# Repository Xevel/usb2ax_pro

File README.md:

# usb2ax_pro
Fast USB interface for robotics servos (Dynamixel)

## License
Code is under MIT License.

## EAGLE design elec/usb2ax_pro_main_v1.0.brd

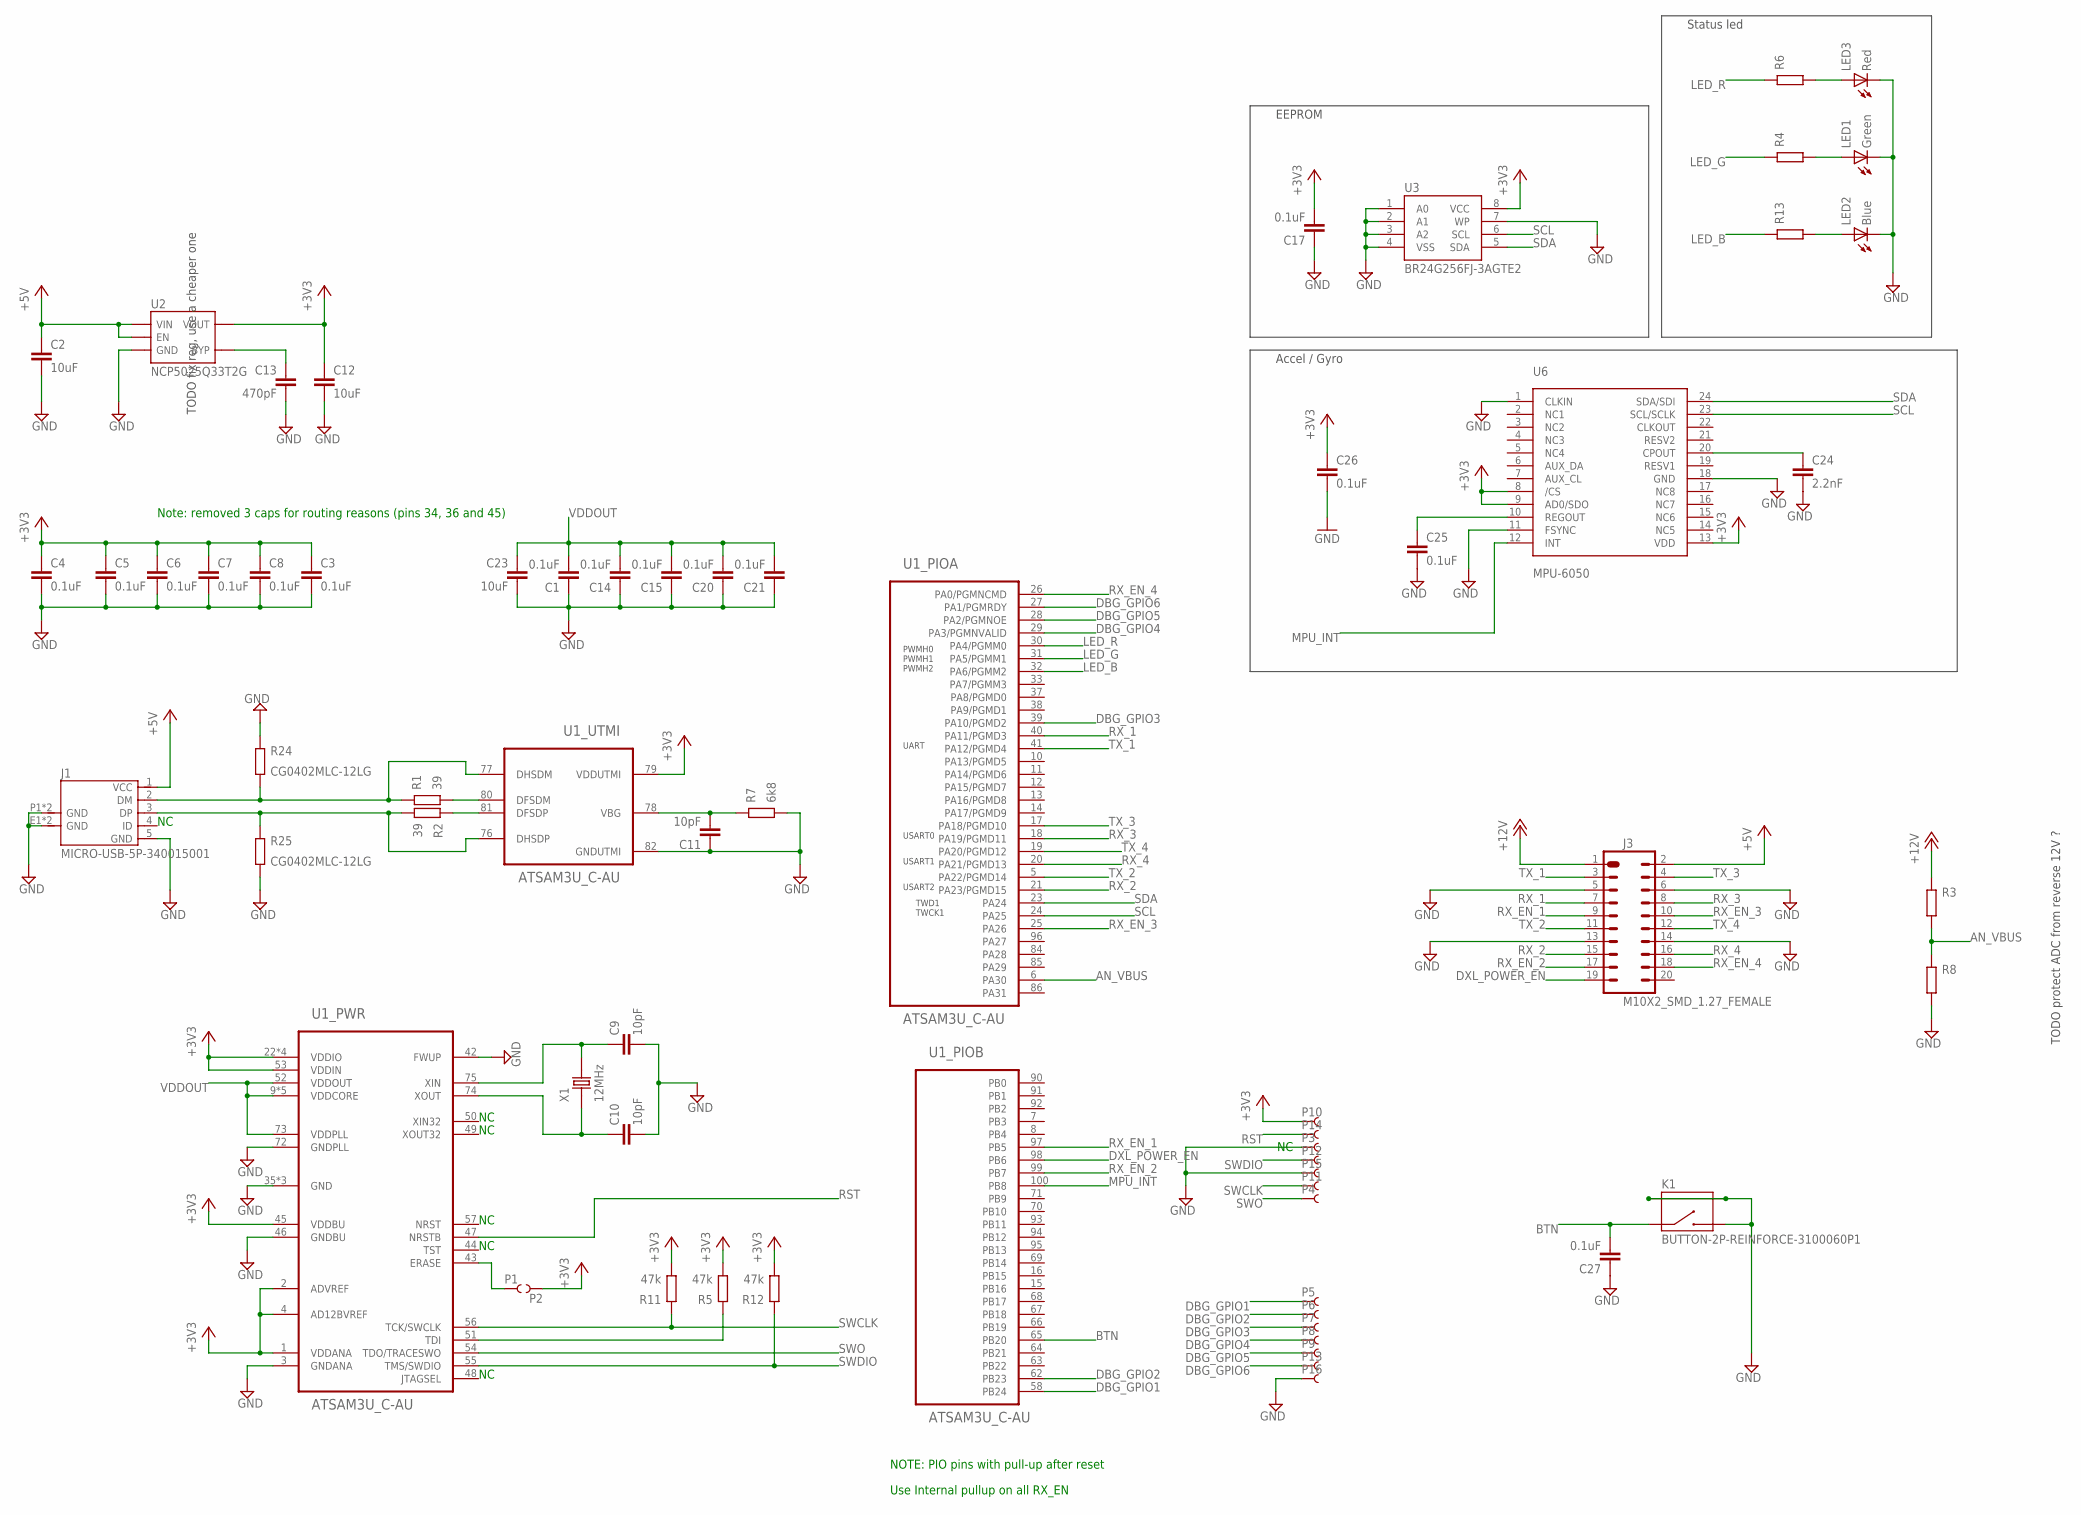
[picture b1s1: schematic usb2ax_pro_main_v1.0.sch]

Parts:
C1, C3, C4, C5, C6, C7, C8, C14, C15, C17, C20, C21, C25, C26, C27: 0.1uF; 0201_N
C2, C12, C23: 10uF; 0805_N
C9, C10, C11: 10pF; 0201_N
C13: 470pF; 0201_N
C24: 2.2nF; 0201_N
J1: MICRO-USB-5P-340015001; B-SMD-5P
J3: M10X2_SMD_1.27_FEMALE; 2X10_SMD_1.27_FEMALE
K1: BUTTON-2P-REINFORCE-3100060P1; 4P-SMD-7.0X3.5X3.5H-90D
LED1: Green; D_0603_N
LED2: Blue; D_0603_N
LED3: Red; D_0603_N
P1, P2: PIN_SMD_2X2.5
P3, P4, P10, P11, P12, P14, P15: PIN_SMD_0.8X1.6
P5, P6, P7, P8, P9, P13, P16: PIN_SMD_1X2
R1, R2: 39; 0201_N
R3, R4, R6, R8, R13: R0201; 0201_N
R5, R11, R12: 47k; 0201_N
R7: 6k8; 0201_N
R24, R25: CG0402MLC-12LG; 0402_N
U1: ATSAM3U_C-AU; QFP50P1600X1600-100N
U2: NCP5025Q33T2G; SC70-5
U3: BR24G256FJ-3AGTE2; SO08
U6: MPU-6050; QFN-24
X1: 12MHz; 2P-SMD-5.0X3.2

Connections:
+3V3: C3.1, C4.1, C5.1, C6.1, C7.1, C8.1, C12.1, C17.2, C26.1, P2.PIN, P10.PIN, R5.1, R11.1, R12.1, U1.1 (VDDANA), U1.2 (ADVREF), U1.4 (AD12BVREF), U1.22 (VDDIO), U1.36 (VDDIO), U1.45 (VDDBU), U1.53 (VDDIN), U1.60 (VDDIO), U1.79 (VDDUTMI), U1.88 (VDDIO), U2.5 (VOUT), U3.8 (VCC), U6.8 (/CS), U6.9 (AD0/SDO), U6.13 (VDD)
+5V: C2.1, J1.1 (VCC), J3.2, U2.1 (VIN), U2.3 (EN)
+12V: J3.1, R3.2
AN_VBUS: R3.1, R8.2, U1.6 (PA30)
BTN: C27.2, K1.1, U1.65 (PB20)
DBG_GPIO1: P5.P$1, U1.58 (PB24)
DBG_GPIO2: P6.P$1, U1.62 (PB23)
DBG_GPIO3: P7.P$1, U1.39 (PA10/PGMD2)
DBG_GPIO4: P8.P$1, U1.29 (PA3/PGMNVALID)
DBG_GPIO5: P9.P$1, U1.28 (PA2/PGMNOE)
DBG_GPIO6: P13.P$1, U1.27 (PA1/PGMRDY)
DXL_POWER_EN: J3.19, U1.98 (PB6)
GND: C1.1, C2.2, C3.2, C4.2, C5.2, C6.2, C7.2, C8.2, C9.2, C10.2, C11.1, C12.2, C13.2, C14.1, C15.1, C17.1, C20.1, C21.1, C23.2, C24.2, C25.2, C26.2, C27.1, J1.5 (GND), J1.E1 (GND), J1.E2 (GND), J1.P1 (GND), J1.P2 (GND), J3.5, J3.6, J3.13, J3.14, K1.2, K1.S1, K1.S2, LED1.C, LED2.C, LED3.C, P3.PIN, P15.PIN, P16.P$1, R7.1, R8.1, R24.2, R25.1, U1.3 (GNDANA), U1.35 (GND), U1.42 (FWUP), U1.46 (GNDBU), U1.61 (GND), U1.72 (GNDPLL), U1.82 (GNDUTMI), U1.89 (GND), U2.2 (GND), U3.1 (A0), U3.2 (A1), U3.3 (A2), U3.4 (VSS), U3.7 (WP), U6.1 (CLKIN), U6.11 (FSYNC), U6.18 (GND)
LED_B: R13.2, U1.32 (PA6/PGMM2)
LED_G: R4.2, U1.31 (PA5/PGMM1)
LED_R: R6.2, U1.30 (PA4/PGMM0)
MPU_INT: U1.100 (PB8), U6.12 (INT)
unnamed: J1.2 (DM), R1.2, R24.1, U1.77 (DHSDM)
unnamed: J1.3 (DP), R2.1, R25.2, U1.76 (DHSDP)
unnamed: R2.2, U1.81 (DFSDP)
unnamed: R1.1, U1.80 (DFSDM)
unnamed: LED3.A, R6.1
unnamed: LED2.A, R13.1
unnamed: LED1.A, R4.1
unnamed: C9.1, U1.75 (XIN), X1.2
unnamed: C10.1, U1.74 (XOUT), X1.1
unnamed: P1.PIN, U1.43 (ERASE)
unnamed: C13.1, U2.4 (BYP)
unnamed: C11.2, R7.2, U1.78 (VBG)
unnamed: C25.1, U6.10 (REGOUT)
unnamed: C24.1, U6.20 (CPOUT)
RST: P14.PIN, U1.47 (NRSTB)
RX_1: J3.7, U1.40 (PA11/PGMD3)
RX_2: J3.15, U1.21 (PA23/PGMD15)
RX_3: J3.8, U1.18 (PA19/PGMD11)
RX_4: J3.16, U1.20 (PA21/PGMD13)
RX_EN_1: J3.9, U1.97 (PB5)
RX_EN_2: J3.17, U1.99 (PB7)
RX_EN_3: J3.10, U1.25 (PA26)
RX_EN_4: J3.18, U1.26 (PA0/PGMNCMD)
SCL: U1.24 (PA25), U3.6 (SCL), U6.23 (SCL/SCLK)
SDA: U1.23 (PA24), U3.5 (SDA), U6.24 (SDA/SDI)
SWCLK: P11.PIN, R11.2, U1.56 (TCK/SWCLK)
SWDIO: P12.PIN, R12.2, U1.55 (TMS/SWDIO)
SWO: P4.PIN, U1.54 (TDO/TRACESWO)
TDI: R5.2, U1.51 (TDI)
TX_1: J3.3, U1.41 (PA12/PGMD4)
TX_2: J3.11, U1.5 (PA22/PGMD14)
TX_3: J3.4, U1.17 (PA18/PGMD10)
TX_4: J3.12, U1.19 (PA20/PGMD12)
VDDOUT: C1.2, C14.2, C15.2, C20.2, C21.2, C23.1, U1.9 (VDDCORE), U1.34 (VDDCORE), U1.52 (VDDOUT), U1.59 (VDDCORE), U1.73 (VDDPLL), U1.83 (VDDCORE), U1.87 (VDDCORE)

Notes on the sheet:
NOTE: PIO pins with pull-up after reset
Status led
Use Internal pullup on all RX_EN
EEPROM
Accel / Gyro
UART
USART0
USART1
USART2
TODO protect ADC from reverse 12V ?
Note: removed 3 caps for routing reasons (pins 34, 36 and 45)
PWMH0 PWMH1 PWMH2
TWD1 TWCK1
TODO fix reg, use a cheaper one

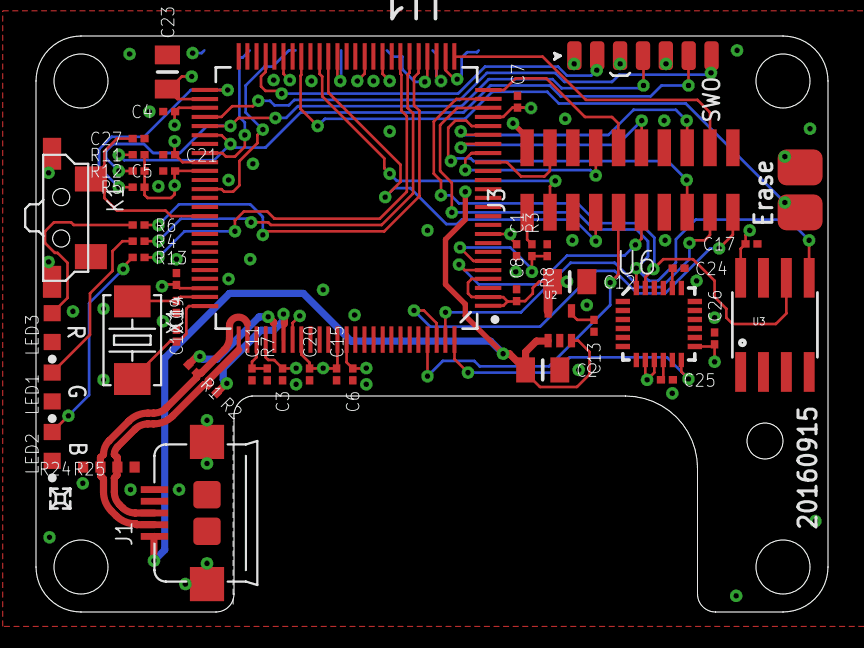
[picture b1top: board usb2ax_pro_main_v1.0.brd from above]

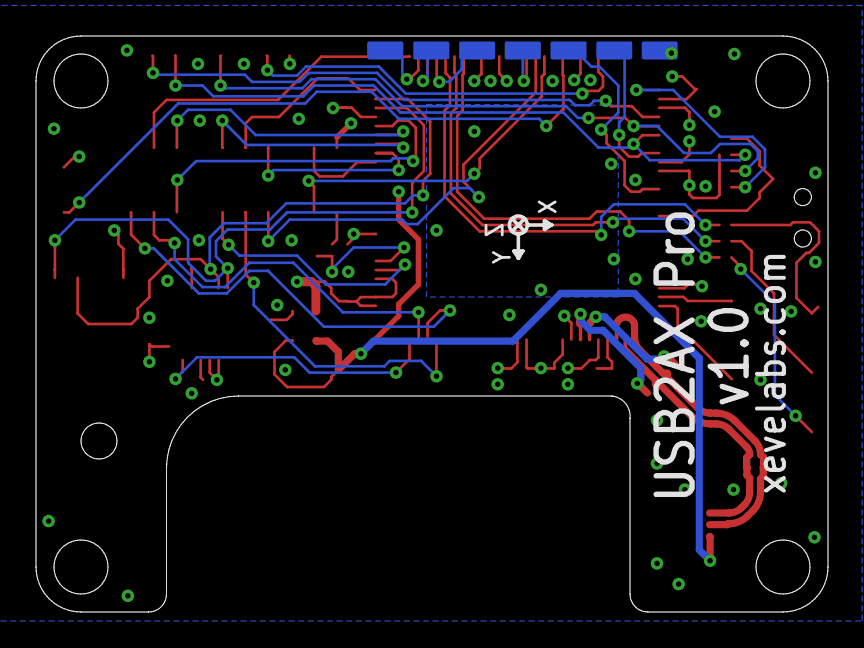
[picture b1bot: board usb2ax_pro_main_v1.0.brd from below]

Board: 4 copper layers, 44.0 x 32.0 mm, 64 parts (7 on the bottom side), 51 nets.

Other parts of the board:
U$3: XEVELABS_LOGO_S

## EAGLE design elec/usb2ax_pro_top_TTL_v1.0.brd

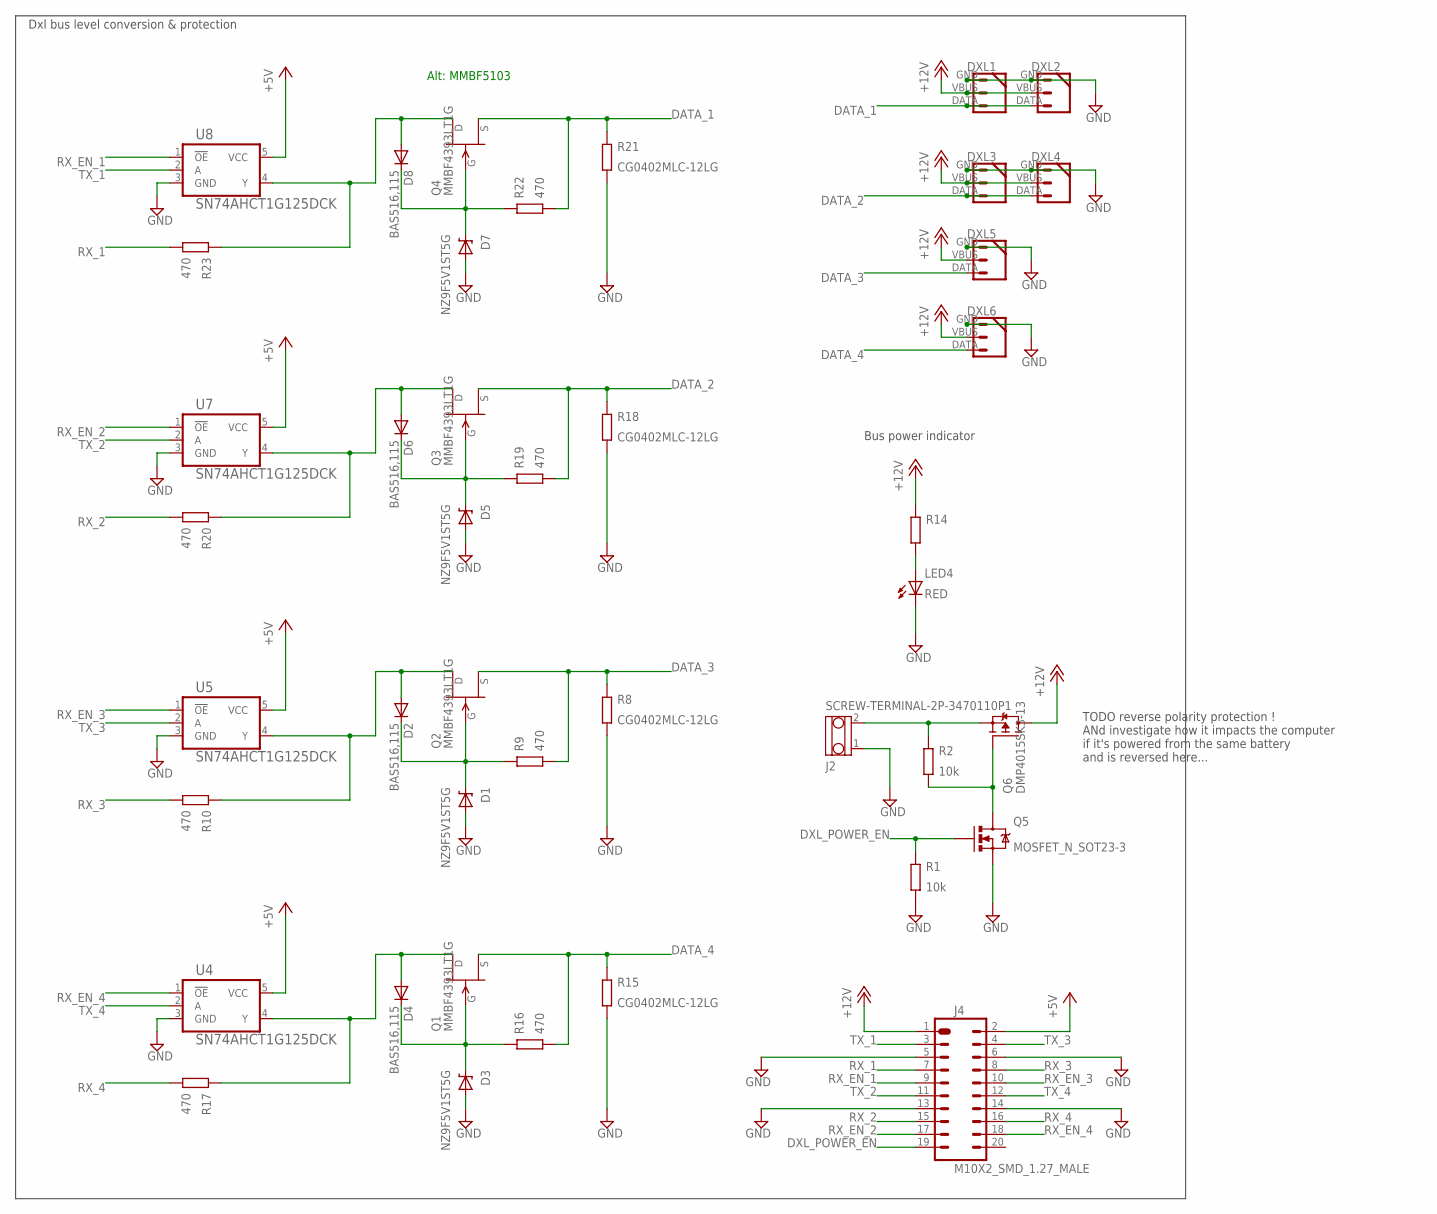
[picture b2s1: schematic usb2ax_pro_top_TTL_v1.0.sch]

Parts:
D1, D3, D5, D7: NZ9F5V1ST5G; SOD-923_N
D2, D4, D6, D8: BAS516,115; SOD523
DXL1, DXL2, DXL3, DXL4, DXL5, DXL6: DYNAMIXEL_3POS-R; DYNAMIXEL_3POS_RIGHT
J2: SCREW-TERMINAL-2P-3470110P1; 2P-5.0
J4: M10X2_SMD_1.27_MALE; 2X10_SMD_1.27_MALE
LED4: RED; D_0603_N
Q1, Q2, Q3, Q4: MMBF4393LT1G; SOT-23-3_L/SSOT-3_L
Q5: MOSFET_N_SOT23-3; SOT-23-3_N/SSOT-3_N
Q6: DMP4015SK3-13; TO252
R1, R2: 10k; 0402_N
R8, R15, R18, R21: CG0402MLC-12LG; 0402_N
R9, R10, R16, R17, R19, R20, R22, R23: 470; 0402_N
R14: R0402; 0402_N
U4, U5, U7, U8: SN74AHCT1G125DCK; SC70-5

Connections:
+5V: J4.2, U4.5 (VCC), U5.5 (VCC), U7.5 (VCC), U8.5 (VCC)
+12V: DXL1.VBUS (2), DXL2.VBUS (2), DXL3.VBUS (2), DXL4.VBUS (2), DXL5.VBUS (2), DXL6.VBUS (2), J4.1, Q6.3 (D), R14.2
DATA_1: DXL1.DATA (3), DXL2.DATA (3), Q4.2 (S), R21.2, R22.1
DATA_2: DXL3.DATA (3), DXL4.DATA (3), Q3.2 (S), R18.2, R19.1
DATA_3: DXL5.DATA (3), Q2.2 (S), R8.2, R9.1
DATA_4: DXL6.DATA (3), Q1.2 (S), R15.2, R16.1
DXL_POWER_EN: J4.19, Q5.1 (G), R1.2
GND: D1.A, D3.A, D5.A, D7.A, DXL1.GND (1), DXL2.GND (1), DXL3.GND (1), DXL4.GND (1), DXL5.GND (1), DXL6.GND (1), J2.1, J4.5, J4.6, J4.13, J4.14, LED4.C, Q5.2 (S), R1.1, R8.1, R15.1, R18.1, R21.1, U4.3 (GND), U5.3 (GND), U7.3 (GND), U8.3 (GND)
unnamed: Q5.3 (D), Q6.1 (G), R2.1
unnamed: D3.C, D4.C, Q1.3 (G), R16.2
unnamed: D1.C, D2.C, Q2.3 (G), R9.2
unnamed: D2.A, Q2.1 (D), R10.2, U5.4 (Y)
unnamed: LED4.A, R14.1
unnamed: D4.A, Q1.1 (D), R17.2, U4.4 (Y)
unnamed: D5.C, D6.C, Q3.3 (G), R19.2
unnamed: D6.A, Q3.1 (D), R20.2, U7.4 (Y)
unnamed: D7.C, D8.C, Q4.3 (G), R22.2
unnamed: J2.2, Q6.2 (S), R2.2
unnamed: D8.A, Q4.1 (D), R23.2, U8.4 (Y)
RX_1: J4.7, R23.1
RX_2: J4.15, R20.1
RX_3: J4.8, R10.1
RX_4: J4.16, R17.1
RX_EN_1: J4.9, U8.1 (!OE)
RX_EN_2: J4.17, U7.1 (!OE)
RX_EN_3: J4.10, U5.1 (!OE)
RX_EN_4: J4.18, U4.1 (!OE)
TX_1: J4.3, U8.2 (A)
TX_2: J4.11, U7.2 (A)
TX_3: J4.4, U5.2 (A)
TX_4: J4.12, U4.2 (A)

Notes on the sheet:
Dxl bus level conversion & protection
Alt: MMBF5103
TODO reverse polarity protection ! ANd investigate how it impacts the computer if it's powered from the same battery and is reversed here...
Bus power indicator

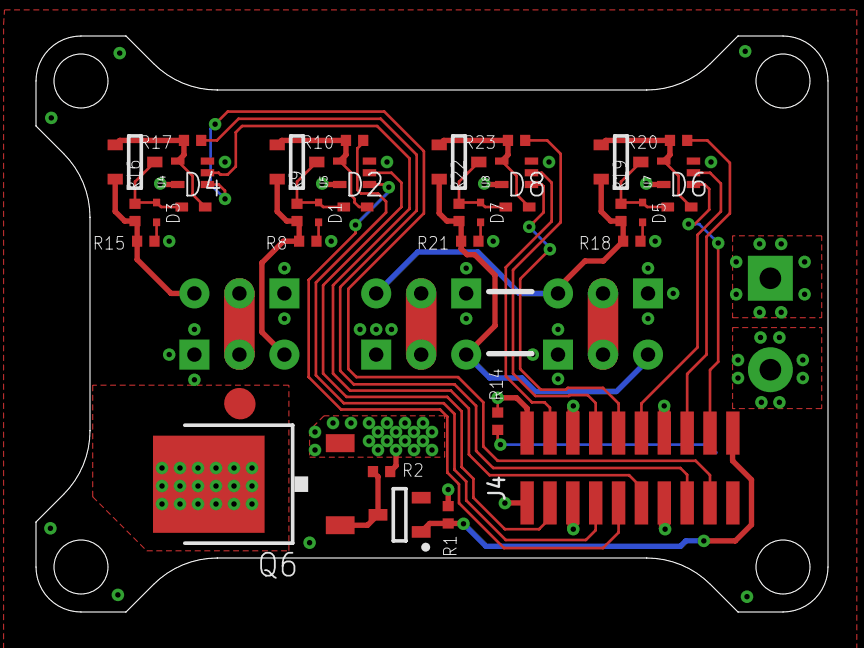
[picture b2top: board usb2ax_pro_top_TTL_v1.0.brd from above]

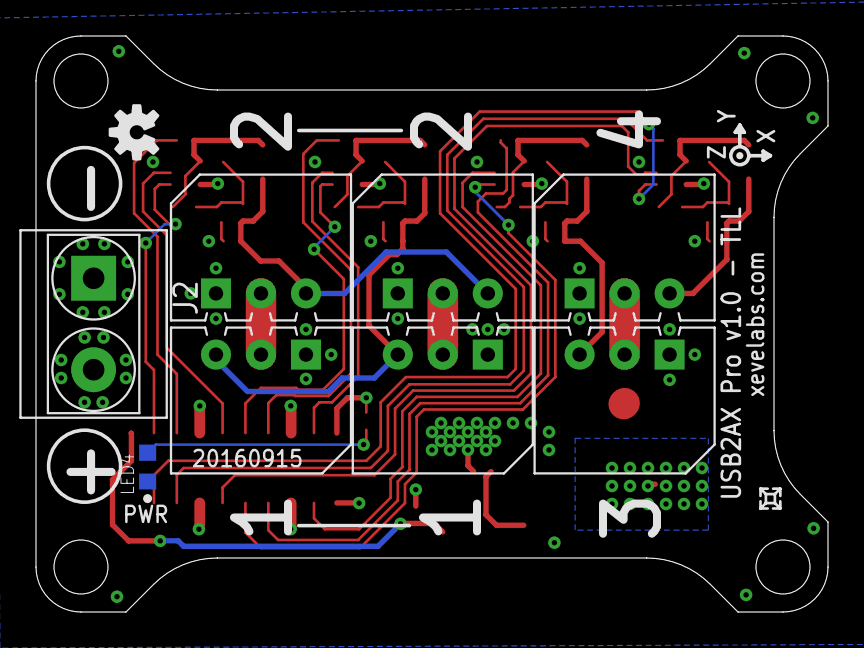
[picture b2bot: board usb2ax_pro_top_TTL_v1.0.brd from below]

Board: 4 copper layers, 44.0 x 32.0 mm, 44 parts (11 on the bottom side), 31 nets.

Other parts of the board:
U$1: XEVELABS_LOGO_S
U$2: OSHW-LOGO-S

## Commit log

2016-09-20 Added license for code
2016-09-20 First version of the boards.
2016-09-20 Fixed 3V3 reg value

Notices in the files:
parts and their libraries:
SparkFun-DigitalIC: Licensing: CC v3.0 Share-Alike You are welcome to use this library for commercial purposes.
